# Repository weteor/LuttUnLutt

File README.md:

### Lütt un Lütt

3x5+2 key split orthogonal BLE keyboard

## Features

- full BLE, powered by coin cells (CR2032)
- choc v1 Hotswap sockets
- encoder
- case files are supplied (stl, dxf, as well as the freecad files)
- ZMK (with dongle support)
- completely open source, permissive license ([CERN-OHL-P](https://cern-ohl.web.cern.ch/home))

### what's left to do?
- fix small hole placement error in case
- fix battery opening in case
- fix cap placement on pcb right

### Want one?

All production files you need to build your own board can be found [here](./prod). they are certainly usable, but the case might need some scraping/cutting to properly fit the battery. I will fix that soon

The case is split in two parts connected by cylindrical 3x1.7mm magnets. The bottom case is open by design and ends at a bit under the hotswap sockets. It's meant to be used with self adhesive neopren sheets (2-3mm thick), which are cut to be the same size as the pcb and then glued on top of the underside of the pcb.

### the rest

Everything in this repository is free to use however you might see fit. If you want to support me and my projects, please consider linking back to this repository if you build/change/use anything.

If you would like to send me a tip, you could do it [here](https://ko-fi.com/weteor) (Please don't feel like you have to).

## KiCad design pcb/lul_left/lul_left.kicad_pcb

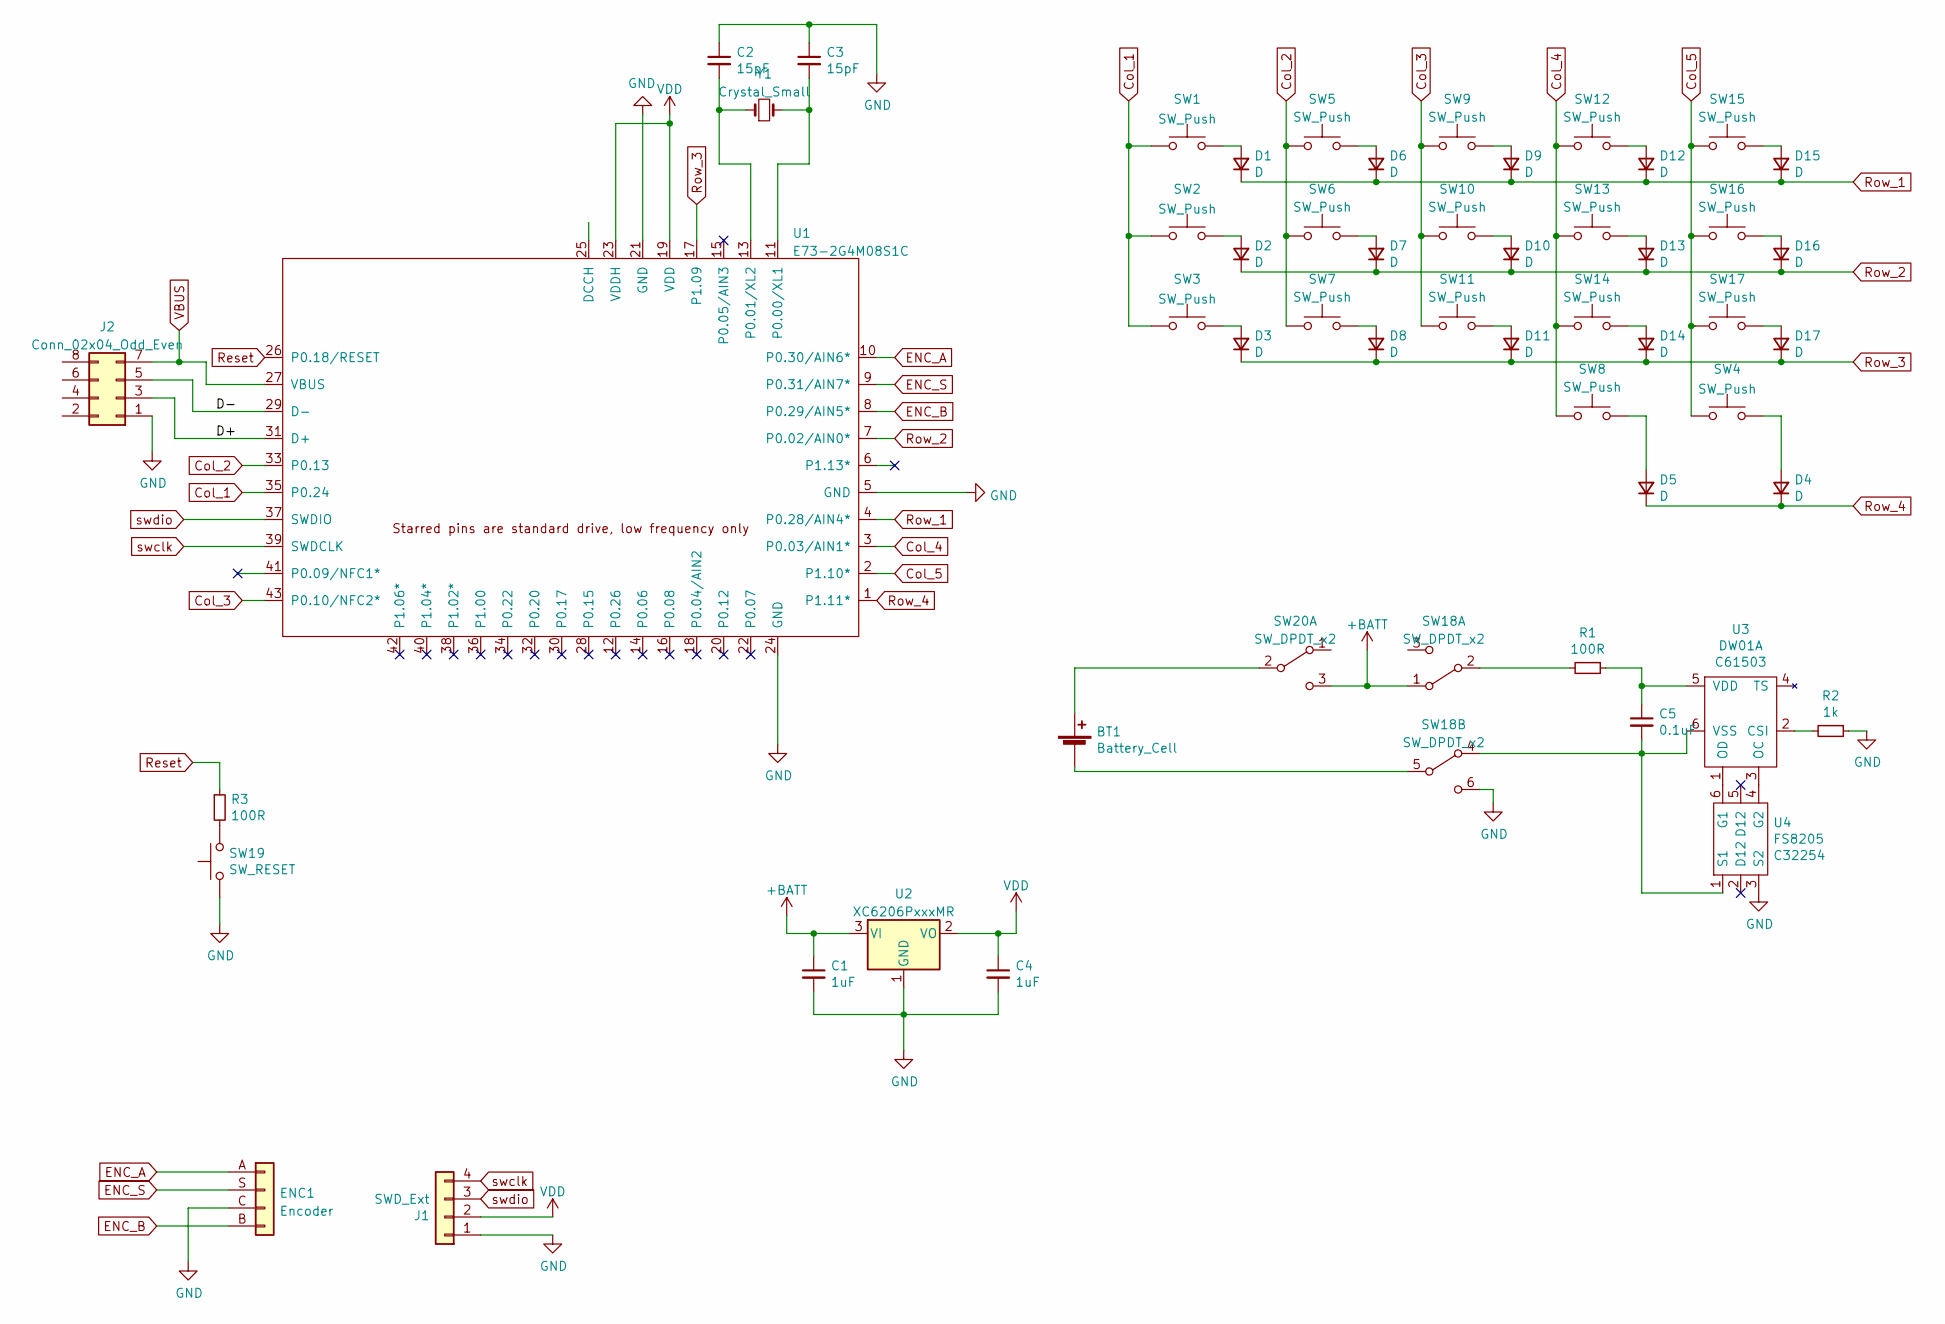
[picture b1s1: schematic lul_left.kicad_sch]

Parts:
BT1: Battery_Cell; Coin Cell 2032
C1, C4: 1uF; C_0603_1608Metric
C2, C3: 15pF; C_0603_1608Metric
C5: 0.1uF; C_0603_1608Metric
D1, D2, D3, D4, D5, D6, D7, D8, D9, D10, D11, D12, D13, D14, D15, D16, D17: D; D_SOD-123
ENC1: Encoder; Mitsumi_SIQ-02FVS3
J1: SWD_Ext; PinHeader_1x04_P2.54mm_Vertical
J2: Conn_02x04_Odd_Even; PinSocket_2x04_P1.27mm_Vertical
R1, R3: 100R; R_0603_1608Metric
R2: 1k; R_0603_1608Metric
SW1, SW2, SW3, SW4, SW5, SW6, SW7, SW9, SW10, SW11, SW12, SW13, SW14, SW15, SW16, SW17: SW_Push; ChocV1_V2_Hotswap_3d
SW8: SW_Push; ChocV1_V2_Hotswap_1.5u
SW18, SW20: SW_DPDT_x2; DPDT - C2837066
SW19: SW_RESET; Micro_Push_Button_3x6x2.5mm
U1: E73-2G4M08S1C; E73-2G4M08S1C_bottom
U2: XC6206PxxxMR; SOT-23
U3: DW01A; SOT-23-6; LCSC C61503
U4: FS8205; SOT-23-6; LCSC C32254
Y1: Crystal_Small; Crystal_SMD_3215-2Pin_3.2x1.5mm

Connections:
+BATT: C1.1, SW18.1 (A), SW20.3 (C), U2.3 (VI)
/D+: J2.3, U1.31 (D+)
/D-: J2.5, U1.29 (D-)
Col_1: SW1.1, SW2.1, SW3.1, U1.35 (P0.24)
Col_2: SW5.1, SW6.1, SW7.1, U1.33 (P0.13)
Col_3: SW9.1, SW10.1, SW11.1, U1.43 (P0.10/NFC2*)
Col_4: SW8.1, SW12.1, SW13.1, SW14.1, U1.3 (P0.03/AIN1*)
Col_5: SW4.1, SW15.1, SW16.1, SW17.1, U1.2 (P1.10*)
ENC_A: ENC1.A, U1.10 (P0.30/AIN6*)
ENC_B: ENC1.B, U1.8 (P0.29/AIN5*)
ENC_S: ENC1.S, U1.9 (P0.31/AIN7*)
GND: C1.2, C2.1, C3.1, C4.2, ENC1.C, J1.1, J2.1, R2.1, SW18.6 (C), SW19.1, U1.5 (GND), U1.21 (GND), U1.24 (GND), U2.1 (GND), U4.3 (S2)
unnamed: BT1.2 (-), SW18.5 (B)
unnamed: C2.2, U1.13 (P0.01/XL2), Y1.1
unnamed: C3.2, U1.11 (P0.00/XL1), Y1.2
unnamed: C5.1, R1.1, U3.5 (VDD)
unnamed: C5.2, SW18.4 (A), U3.6 (VSS), U4.1 (S1)
unnamed: D1.2 (A), SW1.2
unnamed: D2.2 (A), SW2.2
unnamed: D3.2 (A), SW3.2
unnamed: D4.2 (A), SW4.2
unnamed: D5.2 (A), SW8.2
unnamed: D6.2 (A), SW5.2
unnamed: D7.2 (A), SW6.2
unnamed: D8.2 (A), SW7.2
unnamed: D9.2 (A), SW9.2
unnamed: D10.2 (A), SW10.2
unnamed: D11.2 (A), SW11.2
unnamed: D12.2 (A), SW12.2
unnamed: D13.2 (A), SW13.2
unnamed: D14.2 (A), SW14.2
unnamed: D15.2 (A), SW15.2
unnamed: D16.2 (A), SW16.2
unnamed: D17.2 (A), SW17.2
unnamed: R1.2, SW18.2 (B)
unnamed: R2.2, U3.2 (CSI)
unnamed: R3.2, SW19.2
unnamed: BT1.1 (+), SW20.2 (B)
unnamed: U3.1 (OD), U4.6 (G1)
unnamed: U3.3 (OC), U4.4 (G2)
Reset: R3.1, U1.26 (P0.18/RESET)
Row_1: D1.1 (K), D6.1 (K), D9.1 (K), D12.1 (K), D15.1 (K), U1.4 (P0.28/AIN4*)
Row_2: D2.1 (K), D7.1 (K), D10.1 (K), D13.1 (K), D16.1 (K), U1.7 (P0.02/AIN0*)
Row_3: D3.1 (K), D8.1 (K), D11.1 (K), D14.1 (K), D17.1 (K), U1.17 (P1.09)
Row_4: D4.1 (K), D5.1 (K), U1.1 (P1.11*)
VBUS: J2.7, U1.27 (VBUS)
VDD: C4.1, J1.2, U1.19 (VDD), U1.23 (VDDH), U2.2 (VO)
swclk: J1.4, U1.39 (SWDCLK)
swdio: J1.3, U1.37 (SWDIO)

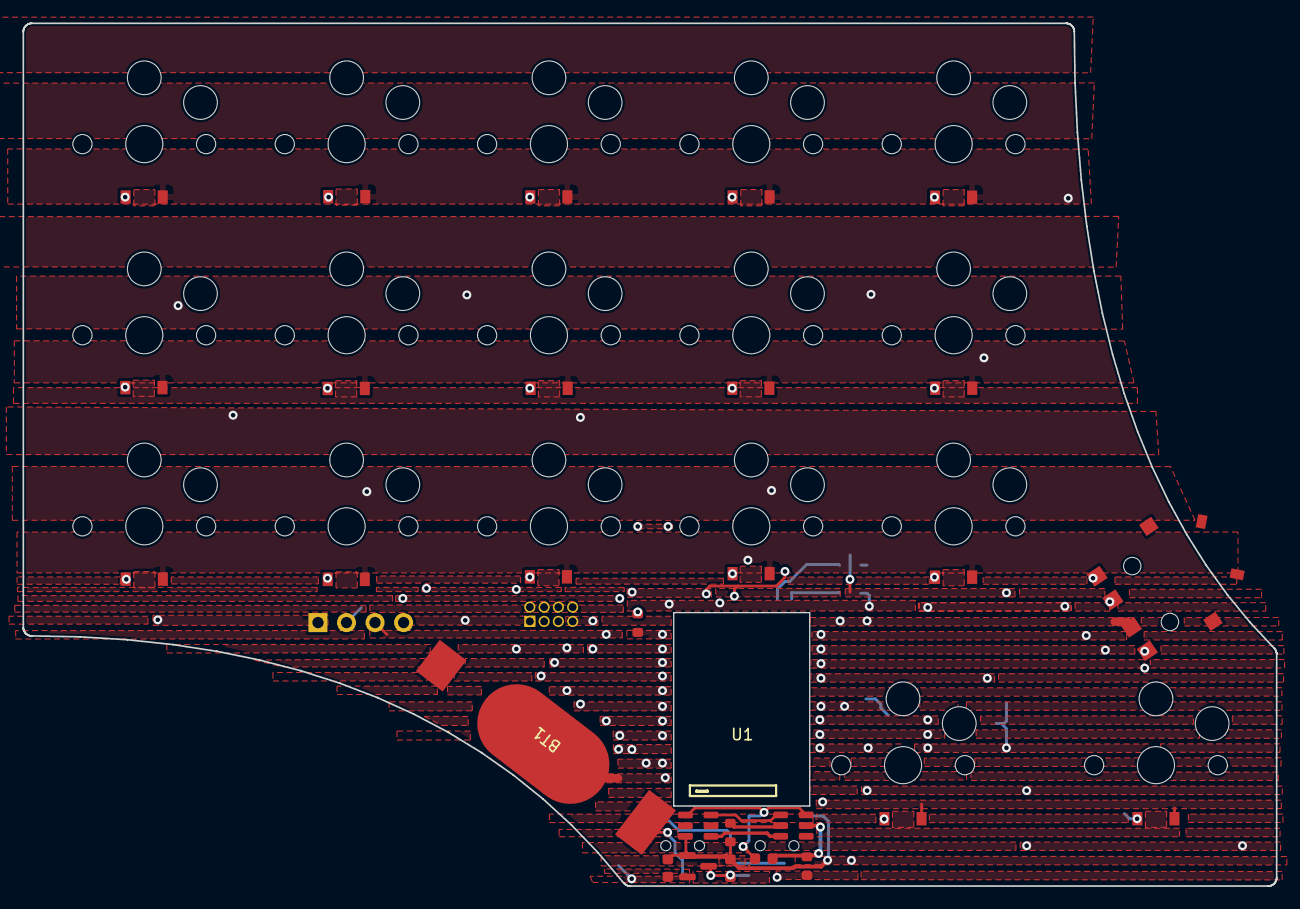
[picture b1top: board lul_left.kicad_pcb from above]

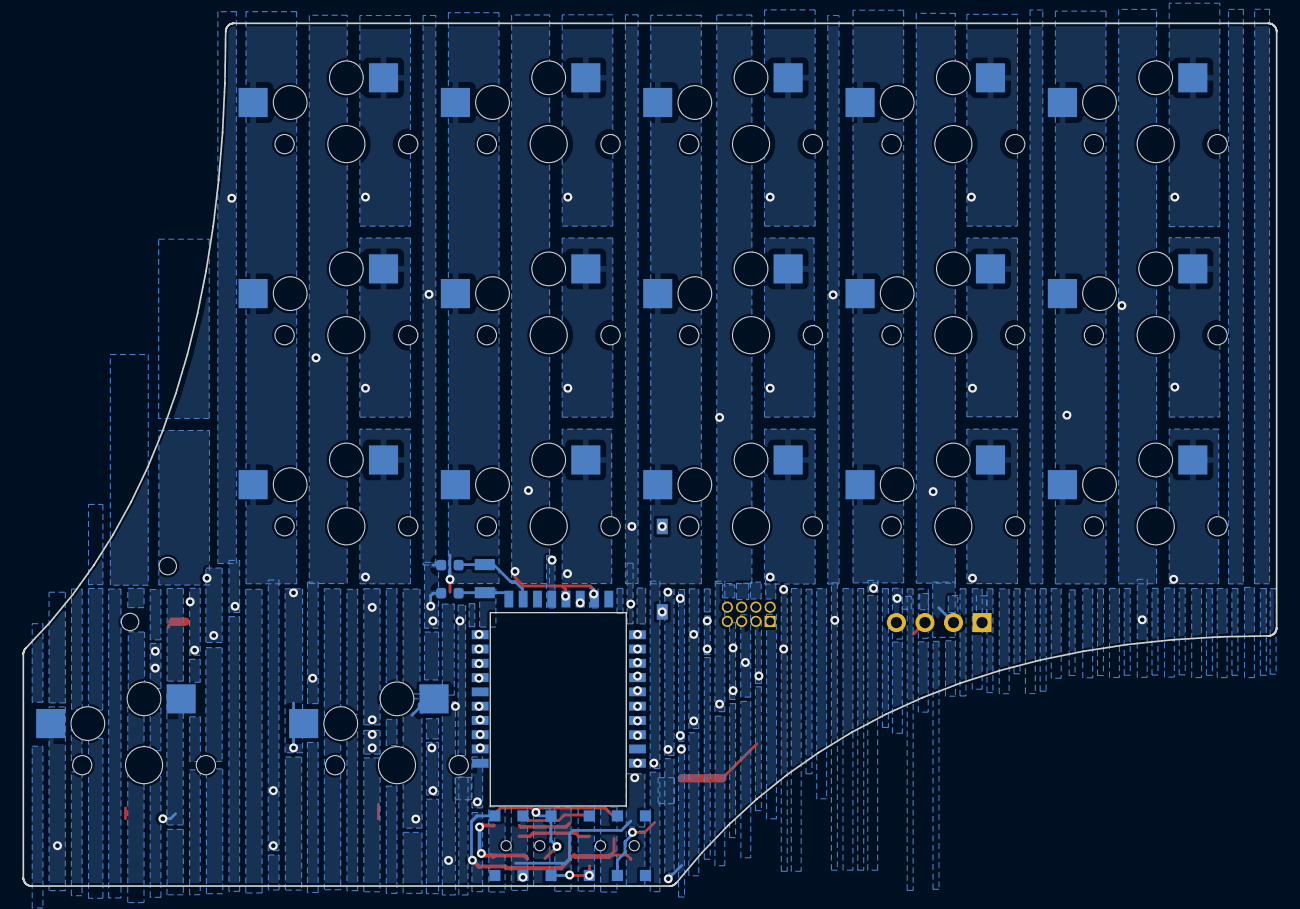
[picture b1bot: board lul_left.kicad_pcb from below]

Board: 2 copper layers, 111.5 x 76.8 mm, 54 parts (7 on the bottom side), 49 nets.

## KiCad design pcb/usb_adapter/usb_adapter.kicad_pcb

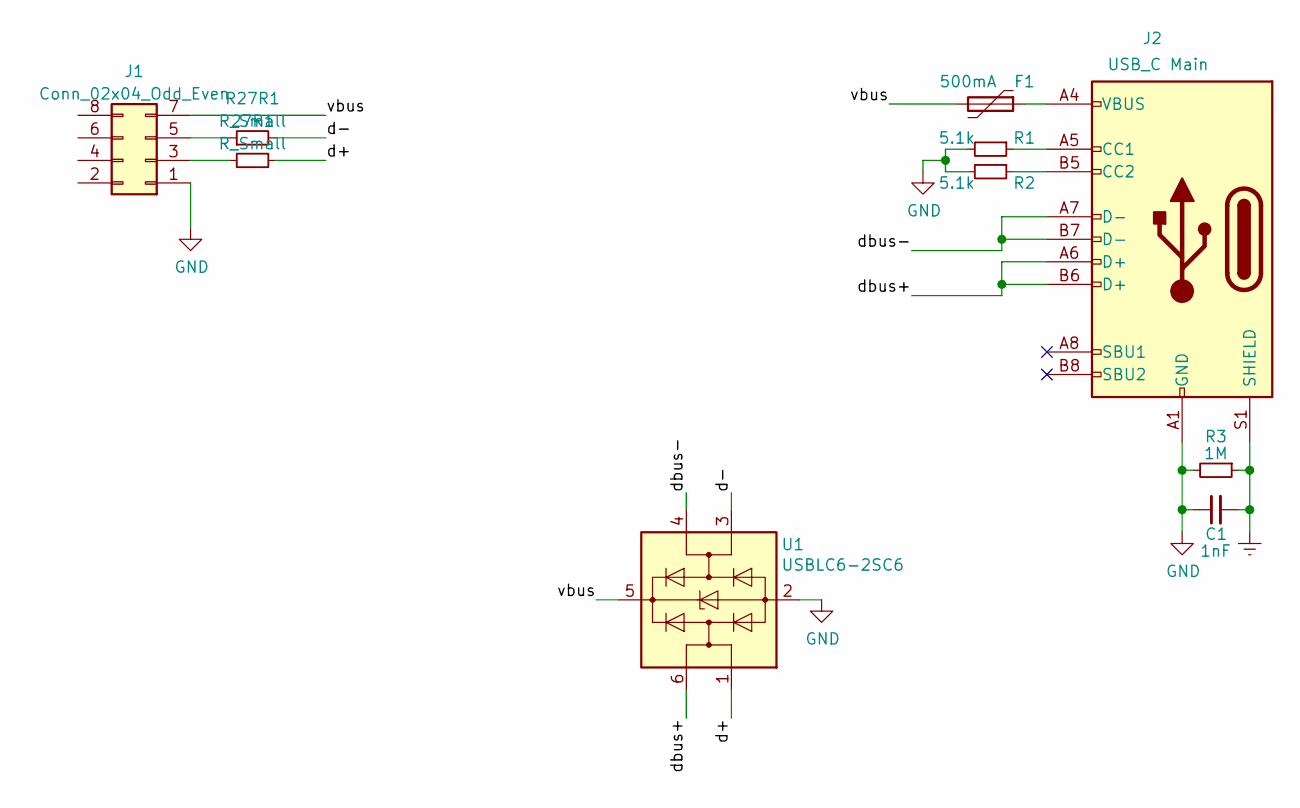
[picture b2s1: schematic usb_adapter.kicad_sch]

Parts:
27R1: R_Small; R_0805_2012Metric
C1: 1nF; C_0805_2012Metric
F1: 500mA; Fuse_1206_3216Metric
J1: Conn_02x04_Odd_Even; PinHeader_2x04_P1.27mm_Horizontal
J2: USB_C Main; USB-C-12-Pin-MidMount
R1, R2: 5.1k; R_0805_2012Metric_Pad1.20x1.40mm_HandSolder
R3: 1M; R_0805_2012Metric_Pad1.20x1.40mm_HandSolder
R27R1: R_Small; R_0805_2012Metric
U1: USBLC6-2SC6; SOT-23-6

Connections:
/d+: 27R1.2, U1.1 (I/O1)
/d-: R27R1.2, U1.3 (I/O2)
/dbus+: J2.A6 (D+), J2.B6 (D+), U1.6 (I/O1)
/dbus-: J2.A7 (D-), J2.B7 (D-), U1.4 (I/O2)
/vbus: F1.2, J1.7, U1.5 (VBUS)
Earth: C1.2, J2.S1 (SHIELD), R3.1
GND: C1.1, J1.1, J2.A1 (GND), J2.A12 (GND), J2.B1 (GND), J2.B12 (GND), R1.2, R2.2, R3.2, U1.2 (GND)
unnamed: 27R1.1, J1.3
unnamed: F1.1, J2.A4 (VBUS), J2.A9 (VBUS), J2.B4 (VBUS), J2.B9 (VBUS)
unnamed: J2.A5 (CC1), R1.1
unnamed: J2.B5 (CC2), R2.1
unnamed: J1.5, R27R1.1

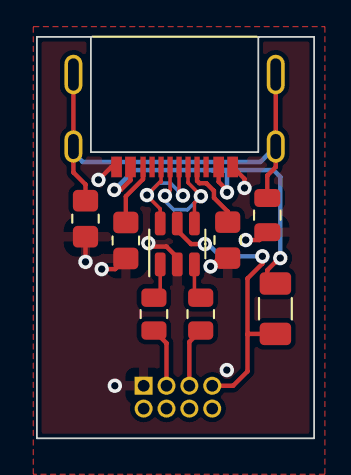
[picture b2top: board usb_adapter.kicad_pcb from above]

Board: 2 copper layers, 15.4 x 22.3 mm, 10 parts (1 on the bottom side), 12 nets.

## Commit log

2023-02-25 add readme and license
2023-02-25 add pcb cad
2023-02-25 add case cad
2023-02-25 add production files
2023-02-25 add img
